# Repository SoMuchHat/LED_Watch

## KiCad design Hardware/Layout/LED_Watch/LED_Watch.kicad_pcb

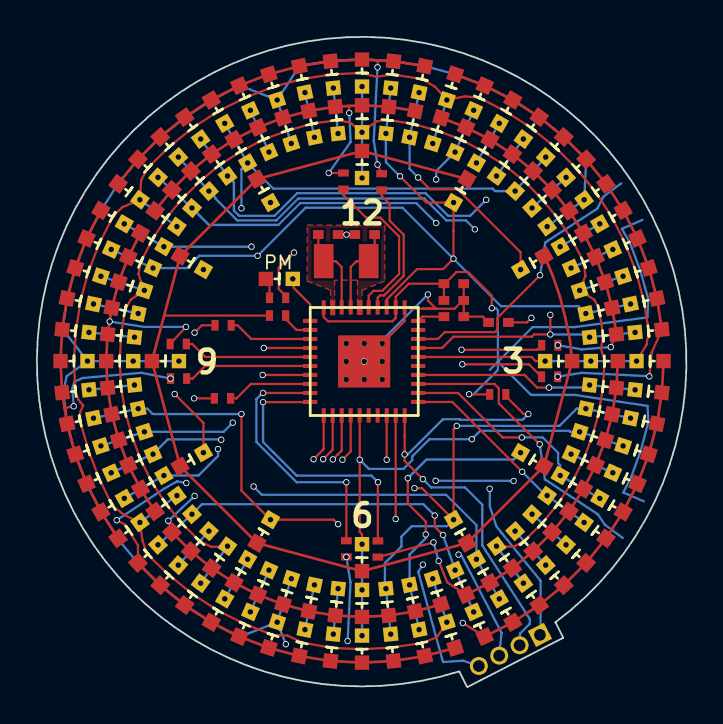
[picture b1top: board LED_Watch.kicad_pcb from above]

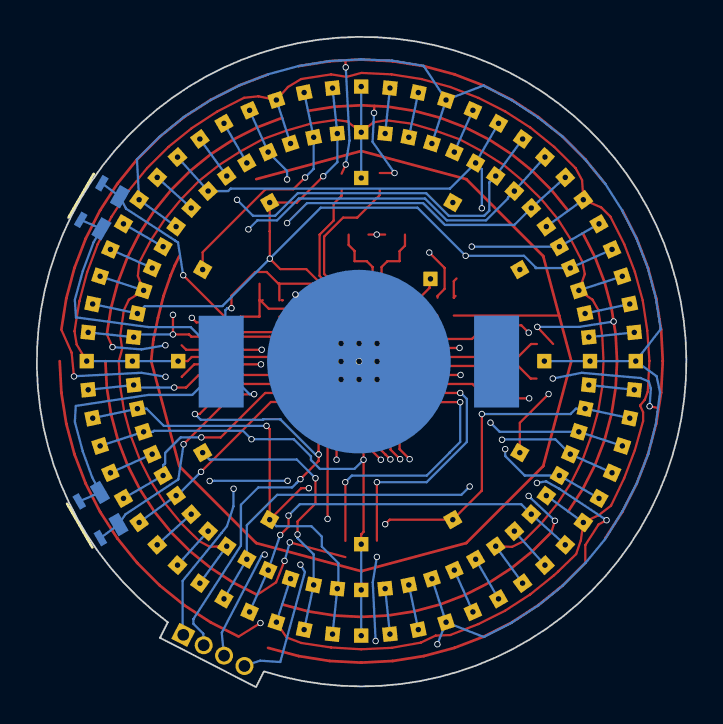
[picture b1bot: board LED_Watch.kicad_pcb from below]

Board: 4 copper layers, 36.1 x 36.1 mm, 158 parts (3 on the bottom side), 46 nets.

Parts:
BT1: CR1216; BAT-HLD-012-SMT
C1: 10uF; C_0402_NoSilk
C2: 0.1uF; C_0402_NoSilk
C3: 1.1nF; C_0402_NoSilk
C4: 470nF; C_0402_NoSilk
C5, C6: 22pF; C_0402_NoSilk
IC1: MSP430FR5721
J1: CONN_01X04; Pin_Header_Straight_1x04_Pitch1.27mm
L1: LED; LSQ976
R1, R3, R4, R5, R6, R7, R8, R9, R10, R11, R12, R13: 200; R_0402_NoSilk
R1C1, R1C2, R1C3, R1C4, R1C5, R1C6, R1C7, R1C8, R1C9, R1C10, R1C11, R1C12, R2C1, R2C2, R2C3, R2C4, R2C5, R2C6, R2C7, R2C8, R2C9, R2C10, R2C11, R2C12, R3C1, R3C2, R3C3, R3C4, R3C5, R3C6, R3C7, R3C8, R3C9, R3C10, R3C11, R3C12, R4C1, R4C2, R4C3, R4C4, R4C5, R4C6, R4C7, R4C8, R4C9, R4C10, R4C11, R4C12, R5C1, R5C2, R5C3, R5C4, R5C5, R5C6, R5C7, R5C8, R5C9, R5C10, R5C11, R5C12, R6C1, R6C2, R6C3, R6C4, R6C5, R6C6, R6C7, R6C8, R6C9, R6C10, R6C11, R6C12, R7C1, R7C2, R7C3, R7C4, R7C5, R7C6, R7C7, R7C8, R7C9, R7C10, R7C11, R7C12, R8C1, R8C2, R8C3, R8C4, R8C5, R8C6, R8C7, R8C8, R8C9, R8C10, R8C11, R8C12, R9C1, R9C2, R9C3, R9C4, R9C5, R9C6, R9C7, R9C8, R9C9, R9C10, R9C11, R9C12, R10C1, R10C2, R10C3, R10C4, R10C5, R10C6, R10C7, R10C8, R10C9, R10C10, R10C11, R10C12, R11C1, R11C2, R11C3, R11C4, R11C5, R11C6, R11C7, R11C8, R11C9, R11C10, R11C11, R11C12: LED; LSQ976
R2: 47k; R_0402_NoSilk
SW1, SW2: SW_Push; EVP-AVAA1A
Y1: Crystal; ABS07

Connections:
+3V3: BT1.1, C1.1, C2.1, IC1.32, IC1.40, J1.1, R2.1, SW1.1, SW2.2
/B1: IC1.28, SW1.2
/B2: IC1.23, SW2.1
/COL1: IC1.26, R1C1.2, R2C1.2, R3C1.2, R4C1.2, R5C1.2, R6C1.2, R7C1.2, R8C1.2, R9C1.2, R10C1.2, R11C1.2
/COL2: IC1.24, R1C2.2, R2C2.2, R3C2.2, R4C2.2, R5C2.2, R6C2.2, R7C2.2, R8C2.2, R9C2.2, R10C2.2, R11C2.2
/COL3: IC1.18, R1C3.2, R2C3.2, R3C3.2, R4C3.2, R5C3.2, R6C3.2, R7C3.2, R8C3.2, R9C3.2, R10C3.2, R11C3.2
/COL4: IC1.15, R1C4.2, R2C4.2, R3C4.2, R4C4.2, R5C4.2, R6C4.2, R7C4.2, R8C4.2, R9C4.2, R10C4.2, R11C4.2
/COL5: IC1.12, R1C5.2, R2C5.2, R3C5.2, R4C5.2, R5C5.2, R6C5.2, R7C5.2, R8C5.2, R9C5.2, R10C5.2, R11C5.2
/COL6: IC1.22, R1C6.2, R2C6.2, R3C6.2, R4C6.2, R5C6.2, R6C6.2, R7C6.2, R8C6.2, R9C6.2, R10C6.2, R11C6.2
/COL7: IC1.21, R1C7.2, R2C7.2, R3C7.2, R4C7.2, R5C7.2, R6C7.2, R7C7.2, R8C7.2, R9C7.2, R10C7.2, R11C7.2
/COL8: IC1.14, R1C8.2, R2C8.2, R3C8.2, R4C8.2, R5C8.2, R6C8.2, R7C8.2, R8C8.2, R9C8.2, R10C8.2, R11C8.2
/COL9: IC1.13, R1C9.2, R2C9.2, R3C9.2, R4C9.2, R5C9.2, R6C9.2, R7C9.2, R8C9.2, R9C9.2, R10C9.2, R11C9.2
/COL10: IC1.11, R1C10.2, R2C10.2, R3C10.2, R4C10.2, R5C10.2, R6C10.2, R7C10.2, R8C10.2, R9C10.2, R10C10.2, R11C10.2
/COL11: IC1.33, R1C11.2, R2C11.2, R3C11.2, R4C11.2, R5C11.2, R6C11.2, R7C11.2, R8C11.2, R9C11.2, R10C11.2, R11C11.2
/COL12: IC1.27, R1C12.2, R2C12.2, R3C12.2, R4C12.2, R5C12.2, R6C12.2, R7C12.2, R8C12.2, R9C12.2, R10C12.2, R11C12.2
/PM_LED: IC1.1, L1.2
/ROW1: IC1.9, R3.1
/ROW2: IC1.10, R4.1
/ROW3: IC1.3, R5.1
/ROW4: IC1.8, R6.1
/ROW5: IC1.6, R7.1
/ROW6: IC1.5, R8.1
/ROW7: IC1.34, R9.1
/ROW8: IC1.35, R10.1
/ROW9: IC1.7, R11.1
/ROW10: IC1.4, R12.1
/ROW11: IC1.2, R13.1
/TCK: IC1.19, J1.3
/TDO: C3.1, IC1.20, J1.2, R2.2
GND: BT1.2, C1.2, C2.2, C3.2, C4.2, C5.1, C6.1, IC1.0, IC1.31, J1.4, R1.2
unnamed: C4.1, IC1.30
unnamed: C5.2, IC1.37, Y1.1
unnamed: C6.2, IC1.38, Y1.2
unnamed: IC1.36, IC1.39
unnamed: L1.1, R1.1
unnamed: R1C1.1, R1C2.1, R1C3.1, R1C4.1, R1C5.1, R1C6.1, R1C7.1, R1C8.1, R1C9.1, R1C10.1, R1C11.1, R1C12.1, R3.2
unnamed: R2C1.1, R2C2.1, R2C3.1, R2C4.1, R2C5.1, R2C6.1, R2C7.1, R2C8.1, R2C9.1, R2C10.1, R2C11.1, R2C12.1, R4.2
unnamed: R3C1.1, R3C2.1, R3C3.1, R3C4.1, R3C5.1, R3C6.1, R3C7.1, R3C8.1, R3C9.1, R3C10.1, R3C11.1, R3C12.1, R5.2
unnamed: R4C1.1, R4C2.1, R4C3.1, R4C4.1, R4C5.1, R4C6.1, R4C7.1, R4C8.1, R4C9.1, R4C10.1, R4C11.1, R4C12.1, R6.2
unnamed: R5C1.1, R5C2.1, R5C3.1, R5C4.1, R5C5.1, R5C6.1, R5C7.1, R5C8.1, R5C9.1, R5C10.1, R5C11.1, R5C12.1, R7.2
unnamed: R6C1.1, R6C2.1, R6C3.1, R6C4.1, R6C5.1, R6C6.1, R6C7.1, R6C8.1, R6C9.1, R6C10.1, R6C11.1, R6C12.1, R8.2
unnamed: R7C1.1, R7C2.1, R7C3.1, R7C4.1, R7C5.1, R7C6.1, R7C7.1, R7C8.1, R7C9.1, R7C10.1, R7C11.1, R7C12.1, R9.2
unnamed: R8C1.1, R8C2.1, R8C3.1, R8C4.1, R8C5.1, R8C6.1, R8C7.1, R8C8.1, R8C9.1, R8C10.1, R8C11.1, R8C12.1, R10.2
unnamed: R10C1.1, R10C2.1, R10C3.1, R10C4.1, R10C5.1, R10C6.1, R10C7.1, R10C8.1, R10C9.1, R10C10.1, R10C11.1, R10C12.1, R12.2
unnamed: R9C1.1, R9C2.1, R9C3.1, R9C4.1, R9C5.1, R9C6.1, R9C7.1, R9C8.1, R9C9.1, R9C10.1, R9C11.1, R9C12.1, R11.2
unnamed: R11C1.1, R11C2.1, R11C3.1, R11C4.1, R11C5.1, R11C6.1, R11C7.1, R11C8.1, R11C9.1, R11C10.1, R11C11.1, R11C12.1, R13.2

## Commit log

2015-08-17 Initial git commit.
    Schematic v0.1
    Board v0.1 (WIP)
    Documentation upload
2015-08-18 Added battery holder documentation Large board layout redesign to prevent vias shorting to pos. battery terminal (WIP)
2015-08-19 Finished laying out board traces. Tactile edge switches may need moved. Added tactile switch datasheet
2015-08-20 Board layout finished (v1.0) Gerbers generated
2015-08-21 Started software. GPIO initialization setup.
2015-08-26 Updated BOM with correct items Added LED Controller.c to easily control which LED is on.
2015-08-26 Added in addition initialization code (clock and RTC) along with RTC and button ISRs
2015-08-27 Added Timer A for button debouncing, expanded button functionality
2015-08-28 Expanded hours array to include PM hours and added PM LED control in all hour functions Added ShowTime code Added SetTime code and functionality to blink current hour/min/sec being changed. Added ini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
2015-08-30 Fixed capacitor values for crystal (9 pF -> 22 pF)
2015-08-30 Modified busy waiting while loops to sleep + interrupt. Fixed bug where blink variable would be enabled but never disabled.
2017-02-23 v1.1 board layout attempt 1
2017-02-23 Flipped everything... could have just flipped MCU. Committing just in case
2017-02-23 Fixed MSP430 mirrored pinout from v1.0
2017-02-27 Improved crystal board layout, added reverse voltage protection with schottky diode. Fixed incorrect capacitor package sizes.
2017-03-16 Expanded board size slightly to ensure switch contacts do not touch LED contacts. Added more silkscreen, fixed size of PM LED
2017-06-11 Latest changes
2017-08-26 Transition to KiCAD for hardware design.
2017-08-28 Design of v1.1 complete. New features: LED light sensing capabilities. Enlarged radius of board slightly. Added "key" for 0.1" pin headers used for programming and to prevent board from rotating in e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
2017-09-30 Working for version of the software that makes use of external oscillator, RTC, and has two different disiplay modes. Does not currently attempt to sleep. Next features: Sleeping to improve energy us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
2017-10-30 Pushing latest firmware written on laptop
2017-10-30 Reduced code size, blinking now working, set time now working. Need to improve button debouncing.
2017-11-02 Complete refactoring of how LEDs are controlled. Now using what I would call "instruction" jump table. Code size reduced, a few bugs were introduced with this change. The dim LED artifact is occuring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
2017-11-04 Fixed dimming light, index corruption, and led jump table to not skip hour 4
2018-02-04 Fixed missing connection between osc and gnd. Fixed disconnected GNDs. Need to fix PM LED to be different LED with appropriate ratings
2018-02-04 Changed PM LED to be the same LED package as others
2018-02-04 Moved debug headers to an offset angle due to watch housing interference.
2018-03-18 Current commit before attempting solution to LEDs not updating during RTC update.
2018-03-20 Fixed LEDs turning off briefly every second. Fixed incorrect LEDs lighting up in display mode 2. Fixed 1 second blink for change time mode.
2018-04-06 Fixed modules so system now enters LPM3.5 successfully and wakes
2018-04-07 Fixed PM LED not showing when in DISPLAY_MODE_2. Cleaned code
2018-04-08 Added light detection and LED dimming functionality
2018-08-01 Updated firmware for v1.1
2018-08-01 Updated PCB to fix last issues with v1.1. PCB changes tested and fully functional
2018-08-01 Merged software and hardware changes. v1.1 complete.
